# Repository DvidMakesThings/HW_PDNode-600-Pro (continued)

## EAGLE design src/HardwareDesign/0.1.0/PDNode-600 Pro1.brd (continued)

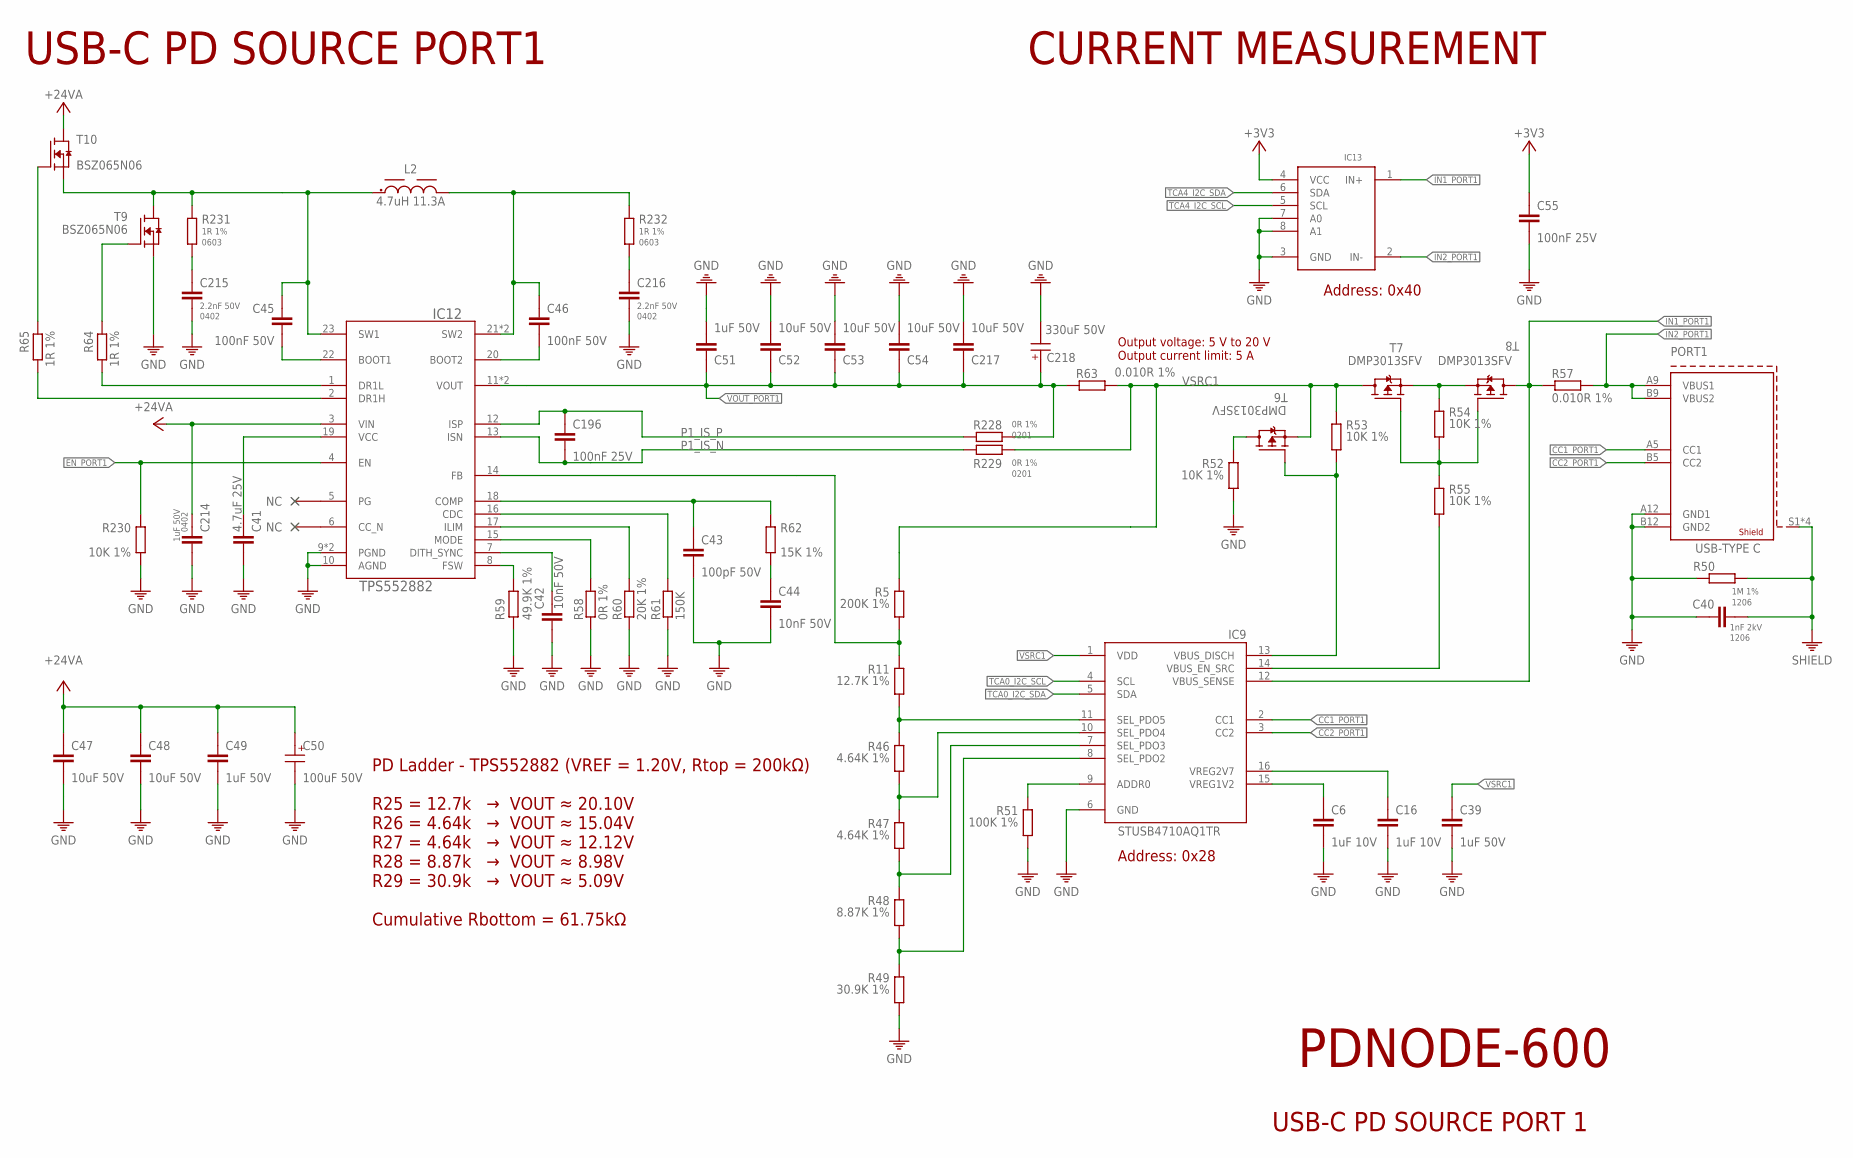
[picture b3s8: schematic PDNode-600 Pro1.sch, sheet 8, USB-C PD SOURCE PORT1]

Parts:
C6, C16: 1uF 10V; 0201
C39: 1uF 50V; 0603
C40: 1nF 2kV; 1206
C41: 4.7uF 25V; 0402
C42, C44: 10nF 50V; 0201
C43: 100pF 50V; 0201
C45, C46: 100nF 50V; 0402
C47, C48, C52, C53, C54, C217: 10uF 50V; 0805
C49: 1uF 50V; 0805
C50: 100uF 50V; 6.3X7.7(DXL)
C51, C214: 1uF 50V; 0402
C55, C196: 100nF 25V; 0201
C215, C216: 2.2nF 50V; 0402
C218: 330uF 50V; 10X10.5(DXL)
IC9: STUSB4710AQ1TR; QFN50P300X300X55-16N
IC12: TPS552882; RPM0026A-MFG
IC13: INA219BIDCNT; SOT23-8
L2: 4.7uH 11.3A; WE-PDHV_1280
PORT1: 632722100213
R5: 200K 1%; 0201
R11: 12.7K 1%; 0201
R46, R47: 4.64K 1%; 0201
R48: 8.87K 1%; 0201
R49: 30.9K 1%; 0201
R50: 1M 1%; 1206
R51: 100K 1%; 0201
R52, R53, R55: 10K 1%; 0402
R54, R230: 10K 1%; 0201
R57, R63: 0.010R 1%; 2512
R58, R228, R229: 0R 1%; 0201
R59: 49.9K 1%; 0201
R60: 20K 1%; 0201
R61: 150K; R0201
R62: 15K 1%; 0201
R64, R65: 1R 1%; 0402
R231, R232: 1R 1%; 0603
T6, T7, T8: DMP3013SFV; POWERDI3333-8_UX_DIO-L
T9, T10: BSZ065N06; POWERDI3333-8_UX_DIO-L

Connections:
+3V3: C55.1, IC13.4 (VCC); also elsewhere on the board
+24V_A: C47.1, C48.1, C49.1, C50.1 (+), C214.1, IC12.3 (VIN), T10.5 (D), T10.6 (D), T10.7 (D), T10.8 (D), T10.9 (D); also elsewhere on the board
CC1_PORT1: IC9.2 (CC1), PORT1.A5 (CC1)
CC2_PORT1: IC9.3 (CC2), PORT1.B5 (CC2)
DISCHARGE1: R52.1, T6.5 (D), T6.6 (D), T6.7 (D), T6.8 (D), T6.9 (D)
EN_PORT1: IC12.4 (EN), R230.1; also elsewhere on the board
GND: C6.2, C16.2, C39.2, C40.1, C41.2, C42.2, C43.2, C44.2, C47.2, C48.2, C49.2, C50.2 (-), C51.2, C52.2, C53.2, C54.2, C55.2, C214.2, C215.2, C216.2, C217.2, C218.2 (-), IC9.6 (GND), IC12.9 (PGND), IC12.10 (AGND), IC12.24 (PGND), IC13.3 (GND), IC13.7 (A0), IC13.8 (A1), PORT1.A12 (GND1), PORT1.B12 (GND2), R49.2, R50.1, R51.2, R52.2, R58.2, R59.2, R60.2, R61.2, R230.2, T9.1 (S), T9.2 (S), T9.3 (S); also elsewhere on the board
IN1_PORT1: IC9.12 (VBUS_SENSE), IC13.1 (IN+), R57.1, T8.5 (D), T8.6 (D), T8.7 (D), T8.8 (D), T8.9 (D)
IN2_PORT1: IC13.2 (IN-), PORT1.A9 (VBUS1), PORT1.B9 (VBUS2), R57.2
IND1: C45.1, IC12.23 (SW1), L2.1, R231.1, T9.5 (D), T9.6 (D), T9.7 (D), T9.8 (D), T9.9 (D), T10.1 (S), T10.2 (S), T10.3 (S)
INDOUT1: C46.1, IC12.21 (SW2), IC12.25 (SW2), L2.2, R232.1
unnamed: IC12.14 (FB), R5.2, R11.1
unnamed: C215.1, R231.2
unnamed: C216.1, R232.2
unnamed: IC9.11 (SEL_PDO5), R11.2, R46.1
unnamed: IC9.10 (SEL_PDO4), R46.2, R47.1
unnamed: IC9.7 (SEL_PDO3), R47.2, R48.1
unnamed: IC9.8 (SEL_PDO2), R48.2, R49.1
unnamed: C6.1, IC9.15 (VREG1V2)
unnamed: C16.1, IC9.16 (VREG2V7)
unnamed: IC9.9 (ADDR0), R51.1
unnamed: IC9.13 (VBUS_DISCH), R53.2, T6.4 (G)
unnamed: R54.2, R55.1, T7.4 (G), T8.4 (G)
unnamed: IC9.14 (VBUS_EN_SRC), R55.2
unnamed: C44.1, R62.2
unnamed: IC12.8 (FSW), R59.1
unnamed: C42.1, IC12.7 (DITH_SYNC)
unnamed: IC12.15 (MODE), R58.1
unnamed: IC12.17 (ILIM), R60.1
unnamed: IC12.16 (CDC), R61.1
unnamed: C43.1, IC12.18 (COMP), R62.1
unnamed: C41.1, IC12.19 (VCC)
unnamed: C45.2, IC12.22 (BOOT1)
unnamed: C46.2, IC12.20 (BOOT2)
unnamed: R65.2, T10.4 (G)
unnamed: R64.2, T9.4 (G)
unnamed: IC12.1 (DR1L), R64.1
unnamed: IC12.2 (DR1H), R65.1
P1_IS_N: C196.2, IC12.13 (ISN), R229.1
P1_IS_P: C196.1, IC12.12 (ISP), R228.1
SHIELD: C40.2, PORT1.S1 (SHIELD1), PORT1.S2 (SHIELD1), PORT1.S3 (SHIELD1), PORT1.S4 (SHIELD1), R50.2; also elsewhere on the board
SOURCE1: R54.1, T7.1 (S), T7.2 (S), T7.3 (S), T8.1 (S), T8.2 (S), T8.3 (S)
TCA0_I2C_SCL: IC9.4 (SCL); also elsewhere on the board
TCA0_I2C_SDA: IC9.5 (SDA); also elsewhere on the board
TCA4_I2C_SCL: IC13.5 (SCL); also elsewhere on the board
TCA4_I2C_SDA: IC13.6 (SDA); also elsewhere on the board
VOUT_PORT1: C51.1, C52.1, C53.1, C54.1, C217.1, C218.1 (+), IC12.11 (VOUT), IC12.26 (VOUT), R63.1, R228.2
VSRC1: C39.1, IC9.1 (VDD), R5.1, R53.1, R63.2, R229.2, T6.1 (S), T6.2 (S), T6.3 (S), T7.5 (D), T7.6 (D), T7.7 (D), T7.8 (D), T7.9 (D)

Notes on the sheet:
USB-C PD SOURCE PORT1
CURRENT MEASUREMENT
Output voltage: 5 V to 20 V Output current limit: 5 A
PD Ladder - TPS552882 (VREF = 1.20V, Rtop = 200kΩ) R25 = 12.7k → VOUT ≈ 20.10V R26 = 4.64k → VOUT ≈ 15.04V R27 = 4.64k → VOUT ≈ 12.12V R28 = 8.87k → VOUT ≈ 8.98V R29 = 30.9k → VOUT ≈ 5.09V Cumulative Rbottom = 61.75kΩ
Address: 0x40
Address: 0x28
USB-C PD SOURCE PORT 1
PDNODE-600

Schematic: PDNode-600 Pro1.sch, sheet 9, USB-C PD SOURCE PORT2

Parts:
C56, C57: 1uF 10V; 0201
C58: 1uF 50V; 0603
C59: 4.7uF 25V; 0402
C60, C62: 10nF 50V; 0201
C61: 100pF 50V; 0201
C63, C64: 100nF 50V; 0402
C65, C66, C70, C71, C72, C78: 10uF 50V; 0805
C67: 1uF 50V; 0805
C68: 100uF 50V; 6.3X7.7(DXL)
C69, C75: 1uF 50V; 0402
C73, C74: 100nF 25V; 0201
C76, C77: 2.2nF 50V; 0402
C79: 330uF 50V; 10X10.5(DXL)
C80: 1nF 2kV; 1206
IC10: TPS552882; RPM0026A-MFG
IC11: INA219BIDCNT; SOT23-8
IC14: STUSB4710AQ1TR; QFN50P300X300X55-16N
L3: 4.7uH 11.3A; WE-PDHV_1280
PORT2: 632722100213
R56: 200K 1%; 0201
R66: 12.7K 1%; 0201
R67, R68: 4.64K 1%; 0201
R69: 8.87K 1%; 0201
R70: 30.9K 1%; 0201
R71: 100K 1%; 0201
R72, R73, R75: 10K 1%; 0402
R74, R88: 10K 1%; 0201
R76, R82: 0.010R 1%; 2512
R77, R86, R87: 0R 1%; 0201
R78: 49.9K 1%; 0201
R79: 20K 1%; 0201
R80: 150K; R0201
R81: 15K 1%; 0201
R83, R85: 1R 1%; 0402
R89, R90: 1R 1%; 0603
R91: 1M 1%; 1206
T1, T2, T3: DMP3013SFV; POWERDI3333-8_UX_DIO-L
T4, T5: BSZ065N06; POWERDI3333-8_UX_DIO-L

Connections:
+3V3: C73.1, IC11.4 (VCC), IC11.7 (A0), R71.2; also elsewhere on the board
+24V_A: C65.1, C66.1, C67.1, C68.1 (+), C75.1, IC10.3 (VIN), T5.5 (D), T5.6 (D), T5.7 (D), T5.8 (D), T5.9 (D); also elsewhere on the board
CC1_PORT2: IC14.2 (CC1), PORT2.A5 (CC1)
CC2_PORT2: IC14.3 (CC2), PORT2.B5 (CC2)
DISCHARGE2: R72.1, T1.5 (D), T1.6 (D), T1.7 (D), T1.8 (D), T1.9 (D)
EN_PORT2: IC10.4 (EN), R88.1; also elsewhere on the board
GND: C56.2, C57.2, C58.2, C59.2, C60.2, C61.2, C62.2, C65.2, C66.2, C67.2, C68.2 (-), C69.2, C70.2, C71.2, C72.2, C73.2, C75.2, C76.2, C77.2, C78.2, C79.2 (-), C80.1, IC10.9 (PGND), IC10.10 (AGND), IC10.24 (PGND), IC11.3 (GND), IC11.8 (A1), IC14.6 (GND), PORT2.A12 (GND1), PORT2.B12 (GND2), R70.2, R72.2, R77.2, R78.2, R79.2, R80.2, R88.2, R91.1, T4.1 (S), T4.2 (S), T4.3 (S); also elsewhere on the board
IN1_PORT2: IC11.1 (IN+), IC14.12 (VBUS_SENSE), R76.1, T3.5 (D), T3.6 (D), T3.7 (D), T3.8 (D), T3.9 (D)
IN2_PORT2: IC11.2 (IN-), PORT2.A9 (VBUS1), PORT2.B9 (VBUS2), R76.2
IND2: C63.1, IC10.23 (SW1), L3.1, R89.1, T4.5 (D), T4.6 (D), T4.7 (D), T4.8 (D), T4.9 (D), T5.1 (S), T5.2 (S), T5.3 (S)
INDOUT2: C64.1, IC10.21 (SW2), IC10.25 (SW2), L3.2, R90.1
unnamed: IC14.11 (SEL_PDO5), R66.2, R67.1
unnamed: IC14.10 (SEL_PDO4), R67.2, R68.1
unnamed: IC14.7 (SEL_PDO3), R68.2, R69.1
unnamed: IC14.8 (SEL_PDO2), R69.2, R70.1
unnamed: C56.1, IC14.15 (VREG1V2)
unnamed: C57.1, IC14.16 (VREG2V7)
unnamed: IC14.9 (ADDR0), R71.1
unnamed: IC14.13 (VBUS_DISCH), R73.2, T1.4 (G)
unnamed: R74.2, R75.1, T2.4 (G), T3.4 (G)
unnamed: IC14.14 (VBUS_EN_SRC), R75.2
unnamed: C62.1, R81.2
unnamed: IC10.8 (FSW), R78.1
unnamed: C60.1, IC10.7 (DITH_SYNC)
unnamed: IC10.15 (MODE), R77.1
unnamed: IC10.17 (ILIM), R79.1
unnamed: IC10.16 (CDC), R80.1
unnamed: C61.1, IC10.18 (COMP), R81.1
unnamed: C59.1, IC10.19 (VCC)
unnamed: C63.2, IC10.22 (BOOT1)
unnamed: C64.2, IC10.20 (BOOT2)
unnamed: R85.2, T5.4 (G)
unnamed: R83.2, T4.4 (G)
unnamed: IC10.1 (DR1L), R83.1
unnamed: IC10.2 (DR1H), R85.1
unnamed: IC10.14 (FB), R56.2, R66.1
unnamed: C76.1, R89.2
unnamed: C77.1, R90.2
P2_IS_N: C74.2, IC10.13 (ISN), R87.1
P2_IS_P: C74.1, IC10.12 (ISP), R86.1
SHIELD: C80.2, PORT2.S1 (SHIELD1), PORT2.S2 (SHIELD1), PORT2.S3 (SHIELD1), PORT2.S4 (SHIELD1), R91.2; also elsewhere on the board
SOURCE2: R74.1, T2.1 (S), T2.2 (S), T2.3 (S), T3.1 (S), T3.2 (S), T3.3 (S)
TCA0_I2C_SCL: IC14.4 (SCL); also elsewhere on the board
TCA0_I2C_SDA: IC14.5 (SDA); also elsewhere on the board
TCA4_I2C_SCL: IC11.5 (SCL); also elsewhere on the board
TCA4_I2C_SDA: IC11.6 (SDA); also elsewhere on the board
VOUT_PORT2: C69.1, C70.1, C71.1, C72.1, C78.1, C79.1 (+), IC10.11 (VOUT), IC10.26 (VOUT), R82.1, R86.2
VSRC2: C58.1, IC14.1 (VDD), R56.1, R73.1, R82.2, R87.2, T1.1 (S), T1.2 (S), T1.3 (S), T2.5 (D), T2.6 (D), T2.7 (D), T2.8 (D), T2.9 (D)

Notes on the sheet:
USB-C PD SOURCE PORT2
CURRENT MEASUREMENT
Output voltage: 5 V to 20 V Output current limit: 5 A
PD Ladder - TPS552882 (VREF = 1.20V, Rtop = 200kΩ) R25 = 12.7k → VOUT ≈ 20.10V R26 = 4.64k → VOUT ≈ 15.04V R27 = 4.64k → VOUT ≈ 12.12V R28 = 8.87k → VOUT ≈ 8.98V R29 = 30.9k → VOUT ≈ 5.09V Cumulative Rbottom = 61.75kΩ
Address: 0x40
Address: 0x28
USB-C PD SOURCE PORT 2
PDNODE-600

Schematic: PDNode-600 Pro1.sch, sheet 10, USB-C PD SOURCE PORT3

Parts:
C81, C86: 1uF 10V; 0201
C87: 1uF 50V; 0603
C88: 4.7uF 25V; 0402
C89, C91: 10nF 50V; 0201
C90: 100pF 50V; 0201
C92, C93: 100nF 50V; 0402
C94, C95, C99, C100, C101, C107: 10uF 50V; 0805
C96: 1uF 50V; 0805
C97: 100uF 50V; 6.3X7.7(DXL)
C98, C104: 1uF 50V; 0402
C102, C103: 100nF 25V; 0201
C105, C106: 2.2nF 50V; 0402
C108: 330uF 50V; 10X10.5(DXL)
C109: 1nF 2kV; 1206
IC15: TPS552882; RPM0026A-MFG
IC16: INA219BIDCNT; SOT23-8
IC17: STUSB4710AQ1TR; QFN50P300X300X55-16N
L4: 4.7uH 11.3A; WE-PDHV_1280
PORT3: 632722100213
R92: 200K 1%; 0201
R93: 12.7K 1%; 0201
R94, R95: 4.64K 1%; 0201
R96: 8.87K 1%; 0201
R97: 30.9K 1%; 0201
R98: 100K 1%; 0201
R99, R100, R102: 10K 1%; 0402
R101, R114: 10K 1%; 0201
R103, R109: 0.010R 1%; 2512
R104, R112, R113: 0R 1%; 0201
R105: 49.9K 1%; 0201
R106: 20K 1%; 0201
R107: 150K; R0201
R108: 15K 1%; 0201
R110, R111: 1R 1%; 0402
R115, R116: 1R 1%; 0603
R117: 1M 1%; 1206
T11, T12, T13: DMP3013SFV; POWERDI3333-8_UX_DIO-L
T14, T15: BSZ065N06; POWERDI3333-8_UX_DIO-L

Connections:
+3V3: C102.1, IC16.4 (VCC), IC16.8 (A1); also elsewhere on the board
+24V_A: C94.1, C95.1, C96.1, C97.1 (+), C104.1, IC15.3 (VIN), T15.5 (D), T15.6 (D), T15.7 (D), T15.8 (D), T15.9 (D); also elsewhere on the board
CC1_PORT3: IC17.2 (CC1), PORT3.A5 (CC1)
CC2_PORT3: IC17.3 (CC2), PORT3.B5 (CC2)
DISCHARGE3: R99.1, T11.5 (D), T11.6 (D), T11.7 (D), T11.8 (D), T11.9 (D)
EN_PORT3: IC15.4 (EN), R114.1; also elsewhere on the board
GND: C81.2, C86.2, C87.2, C88.2, C89.2, C90.2, C91.2, C94.2, C95.2, C96.2, C97.2 (-), C98.2, C99.2, C100.2, C101.2, C102.2, C104.2, C105.2, C106.2, C107.2, C108.2 (-), C109.1, IC15.9 (PGND), IC15.10 (AGND), IC15.24 (PGND), IC16.3 (GND), IC16.7 (A0), IC17.6 (GND), PORT3.A12 (GND1), PORT3.B12 (GND2), R97.2, R98.2, R99.2, R104.2, R105.2, R106.2, R107.2, R114.2, R117.1, T14.1 (S), T14.2 (S), T14.3 (S); also elsewhere on the board
IN1_PORT3: IC16.1 (IN+), IC17.12 (VBUS_SENSE), R103.1, T13.5 (D), T13.6 (D), T13.7 (D), T13.8 (D), T13.9 (D)
IN2_PORT3: IC16.2 (IN-), PORT3.A9 (VBUS1), PORT3.B9 (VBUS2), R103.2
IND3: C92.1, IC15.23 (SW1), L4.1, R115.1, T14.5 (D), T14.6 (D), T14.7 (D), T14.8 (D), T14.9 (D), T15.1 (S), T15.2 (S), T15.3 (S)
INDOUT3: C93.1, IC15.21 (SW2), IC15.25 (SW2), L4.2, R116.1
unnamed: IC17.11 (SEL_PDO5), R93.2, R94.1
unnamed: IC17.10 (SEL_PDO4), R94.2, R95.1
unnamed: IC17.7 (SEL_PDO3), R95.2, R96.1
unnamed: IC17.8 (SEL_PDO2), R96.2, R97.1
unnamed: C81.1, IC17.15 (VREG1V2)
unnamed: C86.1, IC17.16 (VREG2V7)
unnamed: IC17.9 (ADDR0), R98.1
unnamed: IC17.13 (VBUS_DISCH), R100.2, T11.4 (G)
unnamed: R101.2, R102.1, T12.4 (G), T13.4 (G)
unnamed: IC17.14 (VBUS_EN_SRC), R102.2
unnamed: C91.1, R108.2
unnamed: IC15.8 (FSW), R105.1
unnamed: C89.1, IC15.7 (DITH_SYNC)
unnamed: IC15.15 (MODE), R104.1
unnamed: IC15.17 (ILIM), R106.1
unnamed: IC15.16 (CDC), R107.1
unnamed: C90.1, IC15.18 (COMP), R108.1
unnamed: C88.1, IC15.19 (VCC)
unnamed: C92.2, IC15.22 (BOOT1)
unnamed: C93.2, IC15.20 (BOOT2)
unnamed: R111.2, T15.4 (G)
unnamed: R110.2, T14.4 (G)
unnamed: IC15.1 (DR1L), R110.1
unnamed: IC15.2 (DR1H), R111.1
unnamed: IC15.14 (FB), R92.2, R93.1
unnamed: C105.1, R115.2
unnamed: C106.1, R116.2
P3_IS_N: C103.2, IC15.13 (ISN), R113.1
P3_IS_P: C103.1, IC15.12 (ISP), R112.1
SHIELD: C109.2, PORT3.S1 (SHIELD1), PORT3.S2 (SHIELD1), PORT3.S3 (SHIELD1), PORT3.S4 (SHIELD1), R117.2; also elsewhere on the board
SOURCE3: R101.1, T12.1 (S), T12.2 (S), T12.3 (S), T13.1 (S), T13.2 (S), T13.3 (S)
TCA1_I2C_SCL: IC17.4 (SCL); also elsewhere on the board
TCA1_I2C_SDA: IC17.5 (SDA); also elsewhere on the board
TCA4_I2C_SCL: IC16.5 (SCL); also elsewhere on the board
TCA4_I2C_SDA: IC16.6 (SDA); also elsewhere on the board
VOUT_PORT3: C98.1, C99.1, C100.1, C101.1, C107.1, C108.1 (+), IC15.11 (VOUT), IC15.26 (VOUT), R109.1, R112.2
VSRC3: C87.1, IC17.1 (VDD), R92.1, R100.1, R109.2, R113.2, T11.1 (S), T11.2 (S), T11.3 (S), T12.5 (D), T12.6 (D), T12.7 (D), T12.8 (D), T12.9 (D)

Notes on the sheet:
USB-C PD SOURCE PORT3
CURRENT MEASUREMENT
Output voltage: 5 V to 20 V Output current limit: 5 A
PD Ladder - TPS552882 (VREF = 1.20V, Rtop = 200kΩ) R25 = 12.7k → VOUT ≈ 20.10V R26 = 4.64k → VOUT ≈ 15.04V R27 = 4.64k → VOUT ≈ 12.12V R28 = 8.87k → VOUT ≈ 8.98V R29 = 30.9k → VOUT ≈ 5.09V Cumulative Rbottom = 61.75kΩ
Address: 0x40
Address: 0x28
PDNODE-600

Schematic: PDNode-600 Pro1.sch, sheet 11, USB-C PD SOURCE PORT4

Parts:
C110, C111: 1uF 10V; 0201
C112: 1uF 50V; 0603
C113: 4.7uF 25V; 0402
C114, C116: 10nF 50V; 0201
C115: 100pF 50V; 0201
C117, C118: 100nF 50V; 0402
C119, C120, C124, C125, C126, C132: 10uF 50V; 0805
C121: 1uF 50V; 0805
C122: 100uF 50V; 6.3X7.7(DXL)
C123, C129: 1uF 50V; 0402
C127, C128: 100nF 25V; 0201
C130, C131: 2.2nF 50V; 0402
C133: 330uF 50V; 10X10.5(DXL)
C134: 1nF 2kV; 1206
IC18: TPS552882; RPM0026A-MFG
IC19: INA219BIDCNT; SOT23-8
IC20: STUSB4710AQ1TR; QFN50P300X300X55-16N
L5: 4.7uH 11.3A; WE-PDHV_1280
PORT4: 632722100213
R118: 200K 1%; 0201
R119: 12.7K 1%; 0201
R120, R121: 4.64K 1%; 0201
R122: 8.87K 1%; 0201
R123: 30.9K 1%; 0201
R124: 100K 1%; 0201
R125, R126, R128: 10K 1%; 0402
R127, R140: 10K 1%; 0201
R129, R135: 0.010R 1%; 2512
R130, R138, R139: 0R 1%; 0201
R131: 49.9K 1%; 0201
R132: 20K 1%; 0201
R133: 150K; R0201
R134: 15K 1%; 0201
R136, R137: 1R 1%; 0402
R141, R142: 1R 1%; 0603
R143: 1M 1%; 1206
T16, T17, T18: DMP3013SFV; POWERDI3333-8_UX_DIO-L
T19, T20: BSZ065N06; POWERDI3333-8_UX_DIO-L

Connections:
+3V3: C127.1, IC19.4 (VCC), IC19.7 (A0), IC19.8 (A1), R124.2; also elsewhere on the board
+24V_A: C119.1, C120.1, C121.1, C122.1 (+), C129.1, IC18.3 (VIN), T20.5 (D), T20.6 (D), T20.7 (D), T20.8 (D), T20.9 (D); also elsewhere on the board
CC1_PORT4: IC20.2 (CC1), PORT4.A5 (CC1)
CC2_PORT4: IC20.3 (CC2), PORT4.B5 (CC2)
DISCHARGE4: R125.1, T16.5 (D), T16.6 (D), T16.7 (D), T16.8 (D), T16.9 (D)
EN_PORT4: IC18.4 (EN), R140.1; also elsewhere on the board
GND: C110.2, C111.2, C112.2, C113.2, C114.2, C115.2, C116.2, C119.2, C120.2, C121.2, C122.2 (-), C123.2, C124.2, C125.2, C126.2, C127.2, C129.2, C130.2, C131.2, C132.2, C133.2 (-), C134.1, IC18.9 (PGND), IC18.10 (AGND), IC18.24 (PGND), IC19.3 (GND), IC20.6 (GND), PORT4.A12 (GND1), PORT4.B12 (GND2), R123.2, R125.2, R130.2, R131.2, R132.2, R133.2, R140.2, R143.1, T19.1 (S), T19.2 (S), T19.3 (S); also elsewhere on the board
IN1_PORT4: IC19.1 (IN+), IC20.12 (VBUS_SENSE), R129.1, T18.5 (D), T18.6 (D), T18.7 (D), T18.8 (D), T18.9 (D)
IN2_PORT4: IC19.2 (IN-), PORT4.A9 (VBUS1), PORT4.B9 (VBUS2), R129.2
IND4: C117.1, IC18.23 (SW1), L5.1, R141.1, T19.5 (D), T19.6 (D), T19.7 (D), T19.8 (D), T19.9 (D), T20.1 (S), T20.2 (S), T20.3 (S)
INDOUT4: C118.1, IC18.21 (SW2), IC18.25 (SW2), L5.2, R142.1
unnamed: IC20.11 (SEL_PDO5), R119.2, R120.1
unnamed: IC20.10 (SEL_PDO4), R120.2, R121.1
unnamed: IC20.7 (SEL_PDO3), R121.2, R122.1
unnamed: IC20.8 (SEL_PDO2), R122.2, R123.1
unnamed: C110.1, IC20.15 (VREG1V2)
unnamed: C111.1, IC20.16 (VREG2V7)
unnamed: IC20.9 (ADDR0), R124.1
unnamed: IC20.13 (VBUS_DISCH), R126.2, T16.4 (G)
unnamed: R127.2, R128.1, T17.4 (G), T18.4 (G)
unnamed: IC20.14 (VBUS_EN_SRC), R128.2
unnamed: C116.1, R134.2
unnamed: IC18.8 (FSW), R131.1
unnamed: C114.1, IC18.7 (DITH_SYNC)
unnamed: IC18.15 (MODE), R130.1
unnamed: IC18.17 (ILIM), R132.1
unnamed: IC18.16 (CDC), R133.1
unnamed: C115.1, IC18.18 (COMP), R134.1
unnamed: C113.1, IC18.19 (VCC)
unnamed: C117.2, IC18.22 (BOOT1)
unnamed: C118.2, IC18.20 (BOOT2)
unnamed: R137.2, T20.4 (G)
unnamed: R136.2, T19.4 (G)
unnamed: IC18.1 (DR1L), R136.1
unnamed: IC18.2 (DR1H), R137.1
unnamed: IC18.14 (FB), R118.2, R119.1
unnamed: C130.1, R141.2
unnamed: C131.1, R142.2
P4_IS_N: C128.2, IC18.13 (ISN), R139.1
P4_IS_P: C128.1, IC18.12 (ISP), R138.1
SHIELD: C134.2, PORT4.S1 (SHIELD1), PORT4.S2 (SHIELD1), PORT4.S3 (SHIELD1), PORT4.S4 (SHIELD1), R143.2; also elsewhere on the board
SOURCE4: R127.1, T17.1 (S), T17.2 (S), T17.3 (S), T18.1 (S), T18.2 (S), T18.3 (S)
TCA1_I2C_SCL: IC20.4 (SCL); also elsewhere on the board
TCA1_I2C_SDA: IC20.5 (SDA); also elsewhere on the board
TCA4_I2C_SCL: IC19.5 (SCL); also elsewhere on the board
TCA4_I2C_SDA: IC19.6 (SDA); also elsewhere on the board
VOUT_PORT4: C123.1, C124.1, C125.1, C126.1, C132.1, C133.1 (+), IC18.11 (VOUT), IC18.26 (VOUT), R135.1, R138.2
VSRC4: C112.1, IC20.1 (VDD), R118.1, R126.1, R135.2, R139.2, T16.1 (S), T16.2 (S), T16.3 (S), T17.5 (D), T17.6 (D), T17.7 (D), T17.8 (D), T17.9 (D)

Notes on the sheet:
USB-C PD SOURCE PORT4
CURRENT MEASUREMENT
Output voltage: 5 V to 20 V Output current limit: 5 A
PD Ladder - TPS552882 (VREF = 1.20V, Rtop = 200kΩ) R25 = 12.7k → VOUT ≈ 20.10V R26 = 4.64k → VOUT ≈ 15.04V R27 = 4.64k → VOUT ≈ 12.12V R28 = 8.87k → VOUT ≈ 8.98V R29 = 30.9k → VOUT ≈ 5.09V Cumulative Rbottom = 61.75kΩ
Address: 0x40
Address: 0x28
PDNODE-600

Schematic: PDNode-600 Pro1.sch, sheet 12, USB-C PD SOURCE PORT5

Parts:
C135, C136: 1uF 10V; 0201
C137: 1uF 50V; 0603
C138: 4.7uF 25V; 0402
C139, C141: 10nF 50V; 0201
C140: 100pF 50V; 0201
C142, C143: 100nF 50V; 0402
C144, C145, C149, C150, C151, C157: 10uF 50V; 0805
C146: 1uF 50V; 0805
C147: 100uF 50V; 6.3X7.7(DXL)
C148, C154: 1uF 50V; 0402
C152, C153: 100nF 25V; 0201
C155, C156: 2.2nF 50V; 0402
C158: 330uF 50V; 10X10.5(DXL)
C159: 1nF 2kV; 1206
IC21: TPS552882; RPM0026A-MFG
IC22: INA219BIDCNT; SOT23-8
IC23: STUSB4710AQ1TR; QFN50P300X300X55-16N
L6: 4.7uH 11.3A; WE-PDHV_1280
PORT5: 632722100213
R144: 200K 1%; 0201
R145: 12.7K 1%; 0201
R146, R147: 4.64K 1%; 0201
R148: 8.87K 1%; 0201
R149: 30.9K 1%; 0201
R150: 100K 1%; 0201
R151, R152, R154: 10K 1%; 0402
R153, R166: 10K 1%; 0201
R155, R161: 0.010R 1%; 2512
R156, R164, R165: 0R 1%; 0201
R157: 49.9K 1%; 0201
R158: 20K 1%; 0201
R159: 150K; R0201
R160: 15K 1%; 0201
R162, R163: 1R 1%; 0402
R167, R168: 1R 1%; 0603
R169: 1M 1%; 1206
T21, T22, T23: DMP3013SFV; POWERDI3333-8_UX_DIO-L
T24, T25: BSZ065N06; POWERDI3333-8_UX_DIO-L

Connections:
+3V3: C152.1, IC22.4 (VCC); also elsewhere on the board
+24V_B: C144.1, C145.1, C146.1, C147.1 (+), C154.1, IC21.3 (VIN), T25.5 (D), T25.6 (D), T25.7 (D), T25.8 (D), T25.9 (D); also elsewhere on the board
CC1_PORT5: IC23.2 (CC1), PORT5.A5 (CC1)
CC2_PORT5: IC23.3 (CC2), PORT5.B5 (CC2)
DISCHARGE5: R151.1, T21.5 (D), T21.6 (D), T21.7 (D), T21.8 (D), T21.9 (D)
EN_PORT5: IC21.4 (EN), R166.1; also elsewhere on the board
GND: C135.2, C136.2, C137.2, C138.2, C139.2, C140.2, C141.2, C144.2, C145.2, C146.2, C147.2 (-), C148.2, C149.2, C150.2, C151.2, C152.2, C154.2, C155.2, C156.2, C157.2, C158.2 (-), C159.1, IC21.9 (PGND), IC21.10 (AGND), IC21.24 (PGND), IC22.3 (GND), IC22.7 (A0), IC22.8 (A1), IC23.6 (GND), PORT5.A12 (GND1), PORT5.B12 (GND2), R149.2, R150.2, R151.2, R156.2, R157.2, R158.2, R159.2, R166.2, R169.1, T24.1 (S), T24.2 (S), T24.3 (S); also elsewhere on the board
IN1_PORT5: IC22.1 (IN+), IC23.12 (VBUS_SENSE), R155.1, T23.5 (D), T23.6 (D), T23.7 (D), T23.8 (D), T23.9 (D)
IN2_PORT5: IC22.2 (IN-), PORT5.A9 (VBUS1), PORT5.B9 (VBUS2), R155.2
IND5: C142.1, IC21.23 (SW1), L6.1, R167.1, T24.5 (D), T24.6 (D), T24.7 (D), T24.8 (D), T24.9 (D), T25.1 (S), T25.2 (S), T25.3 (S)
INDOUT5: C143.1, IC21.21 (SW2), IC21.25 (SW2), L6.2, R168.1
unnamed: IC23.11 (SEL_PDO5), R145.2, R146.1
unnamed: IC23.10 (SEL_PDO4), R146.2, R147.1
unnamed: IC23.7 (SEL_PDO3), R147.2, R148.1
unnamed: IC23.8 (SEL_PDO2), R148.2, R149.1
unnamed: C135.1, IC23.15 (VREG1V2)
unnamed: C136.1, IC23.16 (VREG2V7)
unnamed: IC23.9 (ADDR0), R150.1
unnamed: IC23.13 (VBUS_DISCH), R152.2, T21.4 (G)
unnamed: R153.2, R154.1, T22.4 (G), T23.4 (G)
unnamed: IC23.14 (VBUS_EN_SRC), R154.2
unnamed: C141.1, R160.2
unnamed: IC21.8 (FSW), R157.1
unnamed: C139.1, IC21.7 (DITH_SYNC)
unnamed: IC21.15 (MODE), R156.1
unnamed: IC21.17 (ILIM), R158.1
unnamed: IC21.16 (CDC), R159.1
unnamed: C140.1, IC21.18 (COMP), R160.1
unnamed: C138.1, IC21.19 (VCC)
unnamed: C142.2, IC21.22 (BOOT1)
unnamed: C143.2, IC21.20 (BOOT2)
unnamed: R163.2, T25.4 (G)
unnamed: R162.2, T24.4 (G)
unnamed: IC21.1 (DR1L), R162.1
unnamed: IC21.2 (DR1H), R163.1
unnamed: IC21.14 (FB), R144.2, R145.1
unnamed: C155.1, R167.2
unnamed: C156.1, R168.2
P5_IS_N: C153.2, IC21.13 (ISN), R165.1
P5_IS_P: C153.1, IC21.12 (ISP), R164.1
SHIELD: C159.2, PORT5.S1 (SHIELD1), PORT5.S2 (SHIELD1), PORT5.S3 (SHIELD1), PORT5.S4 (SHIELD1), R169.2; also elsewhere on the board
SOURCE5: R153.1, T22.1 (S), T22.2 (S), T22.3 (S), T23.1 (S), T23.2 (S), T23.3 (S)
TCA2_I2C_SCL: IC23.4 (SCL); also elsewhere on the board
TCA2_I2C_SDA: IC23.5 (SDA); also elsewhere on the board
TCA5_I2C_SCL: IC22.5 (SCL); also elsewhere on the board
TCA5_I2C_SDA: IC22.6 (SDA); also elsewhere on the board
VOUT_PORT5: C148.1, C149.1, C150.1, C151.1, C157.1, C158.1 (+), IC21.11 (VOUT), IC21.26 (VOUT), R161.1, R164.2
VSRC5: C137.1, IC23.1 (VDD), R144.1, R152.1, R161.2, R165.2, T21.1 (S), T21.2 (S), T21.3 (S), T22.5 (D), T22.6 (D), T22.7 (D), T22.8 (D), T22.9 (D)

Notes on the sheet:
USB-C PD SOURCE PORT5
CURRENT MEASUREMENT
Output voltage: 5 V to 20 V Output current limit: 5 A
PD Ladder - TPS552882 (VREF = 1.20V, Rtop = 200kΩ) R25 = 12.7k → VOUT ≈ 20.10V R26 = 4.64k → VOUT ≈ 15.04V R27 = 4.64k → VOUT ≈ 12.12V R28 = 8.87k → VOUT ≈ 8.98V R29 = 30.9k → VOUT ≈ 5.09V Cumulative Rbottom = 61.75kΩ
Address: 0x40
Address: 0x28
PDNODE-600

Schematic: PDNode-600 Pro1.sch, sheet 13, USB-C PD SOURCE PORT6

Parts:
C160, C161: 1uF 10V; 0201
C162: 1uF 50V; 0603
C163: 4.7uF 25V; 0402
C164, C166: 10nF 50V; 0201
C165: 100pF 50V; 0201
C167, C168: 100nF 50V; 0402
C169, C170, C174, C175, C197, C203: 10uF 50V; 0805
C171: 1uF 50V; 0805
C172: 100uF 50V; 6.3X7.7(DXL)
C173, C200: 1uF 50V; 0402
C198, C199: 100nF 25V; 0201
C201, C202: 2.2nF 50V; 0402
C204: 330uF 50V; 10X10.5(DXL)
C205: 1nF 2kV; 1206
IC24: TPS552882; RPM0026A-MFG
IC25: INA219BIDCNT; SOT23-8
IC30: STUSB4710AQ1TR; QFN50P300X300X55-16N
L7: 4.7uH 11.3A; WE-PDHV_1280
PORT6: 632722100213
R170: 200K 1%; 0201
R171: 12.7K 1%; 0201
R172, R173: 4.64K 1%; 0201
R174: 8.87K 1%; 0201
R175: 30.9K 1%; 0201
R176: 100K 1%; 0201
R177, R178, R180: 10K 1%; 0402
R179, R192: 10K 1%; 0201
R181, R187: 0.010R 1%; 2512
R182, R190, R191: 0R 1%; 0201
R183: 49.9K 1%; 0201
R184: 20K 1%; 0201
R185: 150K; R0201
R186: 15K 1%; 0201
R188, R189: 1R 1%; 0402
R193, R194: 1R 1%; 0603
R195: 1M 1%; 1206
T26, T27, T28: DMP3013SFV; POWERDI3333-8_UX_DIO-L
T29, T30: BSZ065N06; POWERDI3333-8_UX_DIO-L

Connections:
+3V3: C198.1, IC25.4 (VCC), IC25.7 (A0), R176.2; also elsewhere on the board
+24V_B: C169.1, C170.1, C171.1, C172.1 (+), C200.1, IC24.3 (VIN), T30.5 (D), T30.6 (D), T30.7 (D), T30.8 (D), T30.9 (D); also elsewhere on the board
CC1_PORT6: IC30.2 (CC1), PORT6.A5 (CC1)
CC2_PORT6: IC30.3 (CC2), PORT6.B5 (CC2)
DISCHARGE6: R177.1, T26.5 (D), T26.6 (D), T26.7 (D), T26.8 (D), T26.9 (D)
EN_PORT6: IC24.4 (EN), R192.1; also elsewhere on the board
GND: C160.2, C161.2, C162.2, C163.2, C164.2, C165.2, C166.2, C169.2, C170.2, C171.2, C172.2 (-), C173.2, C174.2, C175.2, C197.2, C198.2, C200.2, C201.2, C202.2, C203.2, C204.2 (-), C205.1, IC24.9 (PGND), IC24.10 (AGND), IC24.24 (PGND), IC25.3 (GND), IC25.8 (A1), IC30.6 (GND), PORT6.A12 (GND1), PORT6.B12 (GND2), R175.2, R177.2, R182.2, R183.2, R184.2, R185.2, R192.2, R195.1, T29.1 (S), T29.2 (S), T29.3 (S); also elsewhere on the board
IN1_PORT6: IC25.1 (IN+), IC30.12 (VBUS_SENSE), R181.1, T28.5 (D), T28.6 (D), T28.7 (D), T28.8 (D), T28.9 (D)
IN2_PORT6: IC25.2 (IN-), PORT6.A9 (VBUS1), PORT6.B9 (VBUS2), R181.2
IND6: C167.1, IC24.23 (SW1), L7.1, R193.1, T29.5 (D), T29.6 (D), T29.7 (D), T29.8 (D), T29.9 (D), T30.1 (S), T30.2 (S), T30.3 (S)
INDOUT6: C168.1, IC24.21 (SW2), IC24.25 (SW2), L7.2, R194.1
unnamed: IC30.11 (SEL_PDO5), R171.2, R172.1
unnamed: IC30.10 (SEL_PDO4), R172.2, R173.1
unnamed: IC30.7 (SEL_PDO3), R173.2, R174.1
unnamed: IC30.8 (SEL_PDO2), R174.2, R175.1
unnamed: C160.1, IC30.15 (VREG1V2)
unnamed: C161.1, IC30.16 (VREG2V7)
unnamed: IC30.9 (ADDR0), R176.1
unnamed: IC30.13 (VBUS_DISCH), R178.2, T26.4 (G)
unnamed: R179.2, R180.1, T27.4 (G), T28.4 (G)
unnamed: IC30.14 (VBUS_EN_SRC), R180.2
unnamed: C166.1, R186.2
unnamed: IC24.8 (FSW), R183.1
unnamed: C164.1, IC24.7 (DITH_SYNC)
unnamed: IC24.15 (MODE), R182.1
unnamed: IC24.17 (ILIM), R184.1
unnamed: IC24.16 (CDC), R185.1
unnamed: C165.1, IC24.18 (COMP), R186.1
unnamed: C163.1, IC24.19 (VCC)
unnamed: C167.2, IC24.22 (BOOT1)
unnamed: C168.2, IC24.20 (BOOT2)
unnamed: R189.2, T30.4 (G)
unnamed: R188.2, T29.4 (G)
unnamed: IC24.1 (DR1L), R188.1
unnamed: IC24.2 (DR1H), R189.1
unnamed: IC24.14 (FB), R170.2, R171.1
unnamed: C201.1, R193.2
unnamed: C202.1, R194.2
P6_IS_N: C199.2, IC24.13 (ISN), R191.1
P6_IS_P: C199.1, IC24.12 (ISP), R190.1
SHIELD: C205.2, PORT6.S1 (SHIELD1), PORT6.S2 (SHIELD1), PORT6.S3 (SHIELD1), PORT6.S4 (SHIELD1), R195.2; also elsewhere on the board
SOURCE6: R179.1, T27.1 (S), T27.2 (S), T27.3 (S), T28.1 (S), T28.2 (S), T28.3 (S)
TCA2_I2C_SCL: IC30.4 (SCL); also elsewhere on the board
TCA2_I2C_SDA: IC30.5 (SDA); also elsewhere on the board
TCA5_I2C_SCL: IC25.5 (SCL); also elsewhere on the board
TCA5_I2C_SDA: IC25.6 (SDA); also elsewhere on the board
VOUT_PORT6: C173.1, C174.1, C175.1, C197.1, C203.1, C204.1 (+), IC24.11 (VOUT), IC24.26 (VOUT), R187.1, R190.2
VSRC6: C162.1, IC30.1 (VDD), R170.1, R178.1, R187.2, R191.2, T26.1 (S), T26.2 (S), T26.3 (S), T27.5 (D), T27.6 (D), T27.7 (D), T27.8 (D), T27.9 (D)

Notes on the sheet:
USB-C PD SOURCE PORT6
CURRENT MEASUREMENT
Output voltage: 5 V to 20 V Output current limit: 5 A
PD Ladder - TPS552882 (VREF = 1.20V, Rtop = 200kΩ) R25 = 12.7k → VOUT ≈ 20.10V R26 = 4.64k → VOUT ≈ 15.04V R27 = 4.64k → VOUT ≈ 12.12V R28 = 8.87k → VOUT ≈ 8.98V R29 = 30.9k → VOUT ≈ 5.09V Cumulative Rbottom = 61.75kΩ
Address: 0x40
Address: 0x28
PDNODE-600

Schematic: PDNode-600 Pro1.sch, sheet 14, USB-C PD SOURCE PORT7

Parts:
C206, C207: 1uF 10V; 0201
C208: 1uF 50V; 0603
C209: 4.7uF 25V; 0402
C210, C219: 10nF 50V; 0201
C211: 100pF 50V; 0201
C220, C230: 100nF 50V; 0402
C231, C232, C243, C244, C245, C261: 10uF 50V; 0805
C240: 1uF 50V; 0805
C241: 100uF 50V; 6.3X7.7(DXL)
C242, C258: 1uF 50V; 0402
C246, C250: 100nF 25V; 0201
C259, C260: 2.2nF 50V; 0402
C262: 330uF 50V; 10X10.5(DXL)
C263: 1nF 2kV; 1206
IC32: TPS552882; RPM0026A-MFG
IC33: INA219BIDCNT; SOT23-8
IC34: STUSB4710AQ1TR; QFN50P300X300X55-16N
L8: 4.7uH 11.3A; WE-PDHV_1280
PORT7: 632722100213
R196: 200K 1%; 0201
R197: 12.7K 1%; 0201
R198, R199: 4.64K 1%; 0201
R200: 8.87K 1%; 0201
R201: 30.9K 1%; 0201
R202: 100K 1%; 0201
R203, R204, R219: 10K 1%; 0402
R218, R239: 10K 1%; 0201
R220, R234: 0.010R 1%; 2512
R221, R237, R238: 0R 1%; 0201
R222: 49.9K 1%; 0201
R223: 20K 1%; 0201
R224: 150K; R0201
R233: 15K 1%; 0201
R235, R236: 1R 1%; 0402
R240, R245: 1R 1%; 0603
R246: 1M 1%; 1206
T31, T32, T33: DMP3013SFV; POWERDI3333-8_UX_DIO-L
T34, T35: BSZ065N06; POWERDI3333-8_UX_DIO-L

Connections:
+3V3: C246.1, IC33.4 (VCC), IC33.8 (A1); also elsewhere on the board
+24V_B: C231.1, C232.1, C240.1, C241.1 (+), C258.1, IC32.3 (VIN), T35.5 (D), T35.6 (D), T35.7 (D), T35.8 (D), T35.9 (D); also elsewhere on the board
CC1_PORT7: IC34.2 (CC1), PORT7.A5 (CC1)
CC2_PORT7: IC34.3 (CC2), PORT7.B5 (CC2)
DISCHARGE7: R203.1, T31.5 (D), T31.6 (D), T31.7 (D), T31.8 (D), T31.9 (D)
EN_PORT7: IC32.4 (EN), R239.1; also elsewhere on the board
GND: C206.2, C207.2, C208.2, C209.2, C210.2, C211.2, C219.2, C231.2, C232.2, C240.2, C241.2 (-), C242.2, C243.2, C244.2, C245.2, C246.2, C258.2, C259.2, C260.2, C261.2, C262.2 (-), C263.1, IC32.9 (PGND), IC32.10 (AGND), IC32.24 (PGND), IC33.3 (GND), IC33.7 (A0), IC34.6 (GND), PORT7.A12 (GND1), PORT7.B12 (GND2), R201.2, R202.2, R203.2, R221.2, R222.2, R223.2, R224.2, R239.2, R246.1, T34.1 (S), T34.2 (S), T34.3 (S); also elsewhere on the board
IN1_PORT7: IC33.1 (IN+), IC34.12 (VBUS_SENSE), R220.1, T33.5 (D), T33.6 (D), T33.7 (D), T33.8 (D), T33.9 (D)
IN2_PORT7: IC33.2 (IN-), PORT7.A9 (VBUS1), PORT7.B9 (VBUS2), R220.2
IND7: C220.1, IC32.23 (SW1), L8.1, R240.1, T34.5 (D), T34.6 (D), T34.7 (D), T34.8 (D), T34.9 (D), T35.1 (S), T35.2 (S), T35.3 (S)
INDOUT7: C230.1, IC32.21 (SW2), IC32.25 (SW2), L8.2, R245.1
unnamed: IC34.11 (SEL_PDO5), R197.2, R198.1
unnamed: IC34.10 (SEL_PDO4), R198.2, R199.1
unnamed: IC34.7 (SEL_PDO3), R199.2, R200.1
unnamed: IC34.8 (SEL_PDO2), R200.2, R201.1
unnamed: C206.1, IC34.15 (VREG1V2)
unnamed: C207.1, IC34.16 (VREG2V7)
unnamed: IC34.9 (ADDR0), R202.1
unnamed: IC34.13 (VBUS_DISCH), R204.2, T31.4 (G)
unnamed: R218.2, R219.1, T32.4 (G), T33.4 (G)
unnamed: IC34.14 (VBUS_EN_SRC), R219.2
unnamed: C219.1, R233.2
unnamed: IC32.8 (FSW), R222.1
unnamed: C210.1, IC32.7 (DITH_SYNC)
unnamed: IC32.15 (MODE), R221.1
unnamed: IC32.17 (ILIM), R223.1
unnamed: IC32.16 (CDC), R224.1
unnamed: C211.1, IC32.18 (COMP), R233.1
unnamed: C209.1, IC32.19 (VCC)
unnamed: C220.2, IC32.22 (BOOT1)
unnamed: C230.2, IC32.20 (BOOT2)
unnamed: R236.2, T35.4 (G)
unnamed: R235.2, T34.4 (G)
unnamed: IC32.1 (DR1L), R235.1
unnamed: IC32.2 (DR1H), R236.1
unnamed: IC32.14 (FB), R196.2, R197.1
unnamed: C259.1, R240.2
unnamed: C260.1, R245.2
P7_IS_N: C250.2, IC32.13 (ISN), R238.1
P7_IS_P: C250.1, IC32.12 (ISP), R237.1
SHIELD: C263.2, PORT7.S1 (SHIELD1), PORT7.S2 (SHIELD1), PORT7.S3 (SHIELD1), PORT7.S4 (SHIELD1), R246.2; also elsewhere on the board
SOURCE7: R218.1, T32.1 (S), T32.2 (S), T32.3 (S), T33.1 (S), T33.2 (S), T33.3 (S)
TCA3_I2C_SCL: IC34.4 (SCL); also elsewhere on the board
TCA3_I2C_SDA: IC34.5 (SDA); also elsewhere on the board
TCA5_I2C_SCL: IC33.5 (SCL); also elsewhere on the board
TCA5_I2C_SDA: IC33.6 (SDA); also elsewhere on the board
VOUT_PORT7: C242.1, C243.1, C244.1, C245.1, C261.1, C262.1 (+), IC32.11 (VOUT), IC32.26 (VOUT), R234.1, R237.2
VSRC7: C208.1, IC34.1 (VDD), R196.1, R204.1, R234.2, R238.2, T31.1 (S), T31.2 (S), T31.3 (S), T32.5 (D), T32.6 (D), T32.7 (D), T32.8 (D), T32.9 (D)

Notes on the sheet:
USB-C PD SOURCE PORT7
CURRENT MEASUREMENT
Output voltage: 5 V to 20 V Output current limit: 5 A
PD Ladder - TPS552882 (VREF = 1.20V, Rtop = 200kΩ) R25 = 12.7k → VOUT ≈ 20.10V R26 = 4.64k → VOUT ≈ 15.04V R27 = 4.64k → VOUT ≈ 12.12V R28 = 8.87k → VOUT ≈ 8.98V R29 = 30.9k → VOUT ≈ 5.09V Cumulative Rbottom = 61.75kΩ
Address: 0x40
Address: 0x28
PDNODE-600

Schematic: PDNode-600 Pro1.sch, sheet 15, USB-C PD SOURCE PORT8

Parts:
C265, C266: 1uF 10V; 0201
C267: 1uF 50V; 0603
C268: 4.7uF 25V; 0402
C269, C271: 10nF 50V; 0201
C270: 100pF 50V; 0201
C272, C273: 100nF 50V; 0402
C274, C275, C280, C281, C282, C288: 10uF 50V; 0805
C276: 1uF 50V; 0805
C277: 100uF 50V; 6.3X7.7(DXL)
C279, C285: 1uF 50V; 0402
C283, C284: 100nF 25V; 0201
C286, C287: 2.2nF 50V; 0402
C289: 330uF 50V; 10X10.5(DXL)
C290: 1nF 2kV; 1206
IC35: TPS552882; RPM0026A-MFG
IC36: INA219BIDCNT; SOT23-8
IC37: STUSB4710AQ1TR; QFN50P300X300X55-16N
L9: 4.7uH 11.3A; WE-PDHV_1280
PORT8: 632722100213
R247: 200K 1%; 0201
R248: 12.7K 1%; 0201
R253, R254: 4.64K 1%; 0201
R256: 8.87K 1%; 0201
R257: 30.9K 1%; 0201
R258: 100K 1%; 0201
R259, R260, R262: 10K 1%; 0402
R261, R274: 10K 1%; 0201
R263, R269: 0.010R 1%; 2512
R264, R272, R273: 0R 1%; 0201
R265: 49.9K 1%; 0201
R266: 20K 1%; 0201
R267: 150K; R0201
R268: 15K 1%; 0201
R270, R271: 1R 1%; 0402
R275, R276: 1R 1%; 0603
R277: 1M 1%; 1206
T36, T37, T38: DMP3013SFV; POWERDI3333-8_UX_DIO-L
T39, T40: BSZ065N06; POWERDI3333-8_UX_DIO-L

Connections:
+3V3: C283.1, IC36.4 (VCC), IC36.7 (A0), IC36.8 (A1), R258.2; also elsewhere on the board
+24V_B: C274.1, C275.1, C276.1, C277.1 (+), C285.1, IC35.3 (VIN), T40.5 (D), T40.6 (D), T40.7 (D), T40.8 (D), T40.9 (D); also elsewhere on the board
CC1_PORT8: IC37.2 (CC1), PORT8.A5 (CC1)
CC2_PORT8: IC37.3 (CC2), PORT8.B5 (CC2)
DISCHARGE8: R259.1, T36.5 (D), T36.6 (D), T36.7 (D), T36.8 (D), T36.9 (D)
EN_PORT8: IC35.4 (EN), R274.1; also elsewhere on the board
GND: C265.2, C266.2, C267.2, C268.2, C269.2, C270.2, C271.2, C274.2, C275.2, C276.2, C277.2 (-), C279.2, C280.2, C281.2, C282.2, C283.2, C285.2, C286.2, C287.2, C288.2, C289.2 (-), C290.1, IC35.9 (PGND), IC35.10 (AGND), IC35.24 (PGND), IC36.3 (GND), IC37.6 (GND), PORT8.A12 (GND1), PORT8.B12 (GND2), R257.2, R259.2, R264.2, R265.2, R266.2, R267.2, R274.2, R277.1, T39.1 (S), T39.2 (S), T39.3 (S); also elsewhere on the board
IN1_PORT8: IC36.1 (IN+), IC37.12 (VBUS_SENSE), R263.1, T38.5 (D), T38.6 (D), T38.7 (D), T38.8 (D), T38.9 (D)
IN2_PORT8: IC36.2 (IN-), PORT8.A9 (VBUS1), PORT8.B9 (VBUS2), R263.2
IND8: C272.1, IC35.23 (SW1), L9.1, R275.1, T39.5 (D), T39.6 (D), T39.7 (D), T39.8 (D), T39.9 (D), T40.1 (S), T40.2 (S), T40.3 (S)
INDOUT8: C273.1, IC35.21 (SW2), IC35.25 (SW2), L9.2, R276.1
unnamed: IC37.11 (SEL_PDO5), R248.2, R253.1
unnamed: IC37.10 (SEL_PDO4), R253.2, R254.1
unnamed: IC37.7 (SEL_PDO3), R254.2, R256.1
unnamed: IC37.8 (SEL_PDO2), R256.2, R257.1
unnamed: C265.1, IC37.15 (VREG1V2)
unnamed: C266.1, IC37.16 (VREG2V7)
unnamed: IC37.9 (ADDR0), R258.1
unnamed: IC37.13 (VBUS_DISCH), R260.2, T36.4 (G)
unnamed: R261.2, R262.1, T37.4 (G), T38.4 (G)
unnamed: IC37.14 (VBUS_EN_SRC), R262.2
unnamed: C271.1, R268.2
unnamed: IC35.8 (FSW), R265.1
unnamed: C269.1, IC35.7 (DITH_SYNC)
unnamed: IC35.15 (MODE), R264.1
unnamed: IC35.17 (ILIM), R266.1
unnamed: IC35.16 (CDC), R267.1
unnamed: C270.1, IC35.18 (COMP), R268.1
unnamed: C268.1, IC35.19 (VCC)
unnamed: C272.2, IC35.22 (BOOT1)
unnamed: C273.2, IC35.20 (BOOT2)
unnamed: R271.2, T40.4 (G)
unnamed: R270.2, T39.4 (G)
unnamed: IC35.1 (DR1L), R270.1
unnamed: IC35.2 (DR1H), R271.1
unnamed: IC35.14 (FB), R247.2, R248.1
unnamed: C286.1, R275.2
unnamed: C287.1, R276.2
P8_IS_N: C284.2, IC35.13 (ISN), R273.1
P8_IS_P: C284.1, IC35.12 (ISP), R272.1
SHIELD: C290.2, PORT8.S1 (SHIELD1), PORT8.S2 (SHIELD1), PORT8.S3 (SHIELD1), PORT8.S4 (SHIELD1), R277.2; also elsewhere on the board
SOURCE8: R261.1, T37.1 (S), T37.2 (S), T37.3 (S), T38.1 (S), T38.2 (S), T38.3 (S)
TCA3_I2C_SCL: IC37.4 (SCL); also elsewhere on the board
TCA3_I2C_SDA: IC37.5 (SDA); also elsewhere on the board
TCA5_I2C_SCL: IC36.5 (SCL); also elsewhere on the board
TCA5_I2C_SDA: IC36.6 (SDA); also elsewhere on the board
VOUT_PORT8: C279.1, C280.1, C281.1, C282.1, C288.1, C289.1 (+), IC35.11 (VOUT), IC35.26 (VOUT), R269.1, R272.2
VSRC8: C267.1, IC37.1 (VDD), R247.1, R260.1, R269.2, R273.2, T36.1 (S), T36.2 (S), T36.3 (S), T37.5 (D), T37.6 (D), T37.7 (D), T37.8 (D), T37.9 (D)

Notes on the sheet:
USB-C PD SOURCE PORT8
CURRENT MEASUREMENT
Output voltage: 5 V to 20 V Output current limit: 5 A
PD Ladder - TPS552882 (VREF = 1.20V, Rtop = 200kΩ) R25 = 12.7k → VOUT ≈ 20.10V R26 = 4.64k → VOUT ≈ 15.04V R27 = 4.64k → VOUT ≈ 12.12V R28 = 8.87k → VOUT ≈ 8.98V R29 = 30.9k → VOUT ≈ 5.09V Cumulative Rbottom = 61.75kΩ
Address: 0x40
Address: 0x28
PDNODE-600
